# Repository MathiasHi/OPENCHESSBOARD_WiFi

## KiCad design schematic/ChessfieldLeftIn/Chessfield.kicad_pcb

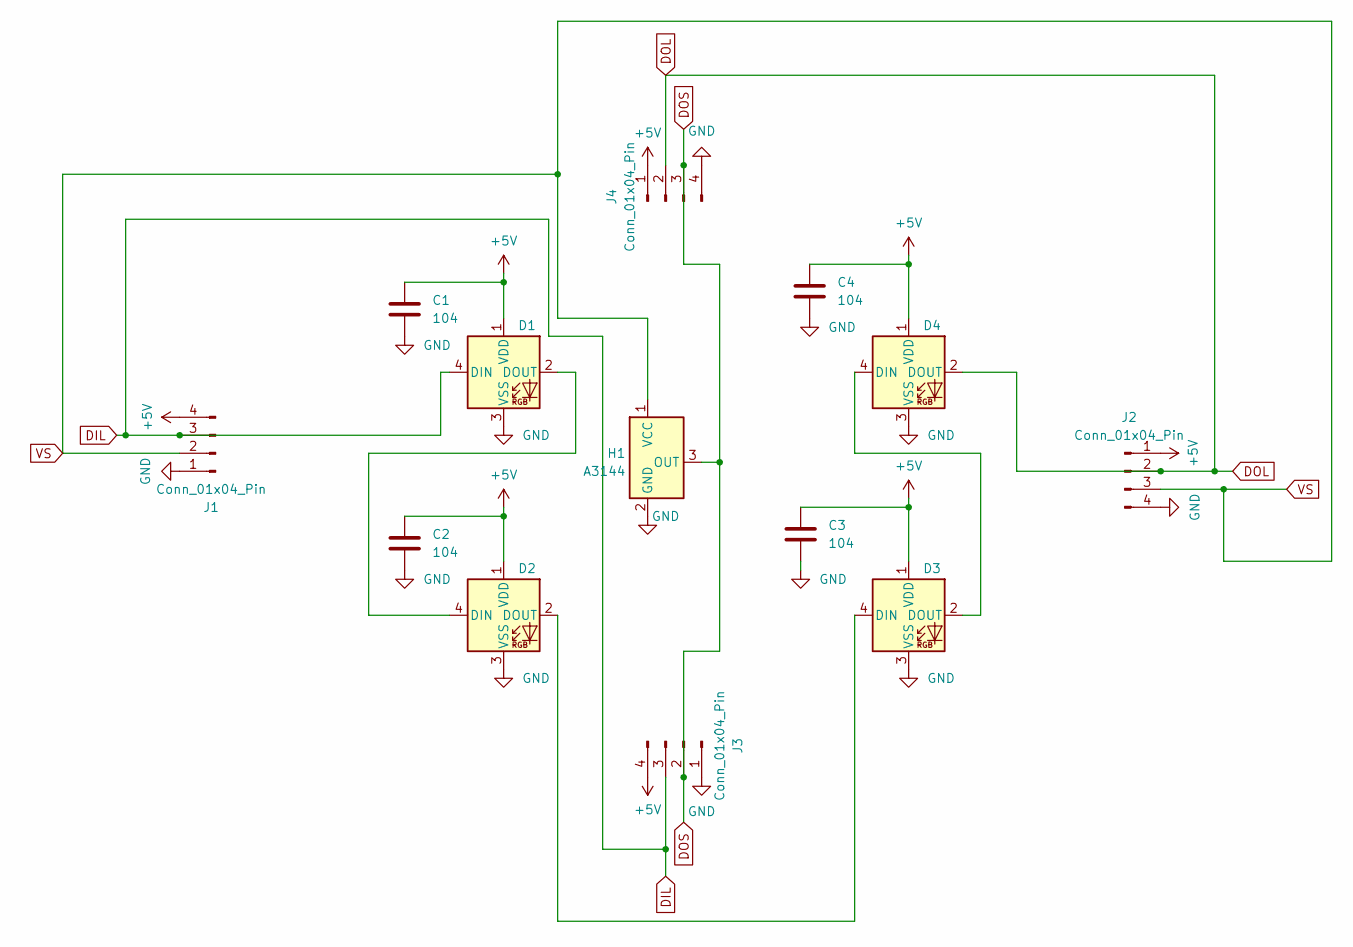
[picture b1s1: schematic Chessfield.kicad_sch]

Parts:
C1, C2, C3, C4: 104; C_0603_1608Metric_Pad1.08x0.95mm_HandSolder
D1, D2, D3, D4: WS2812B; LED_WS2812B_PLCC4_5.0x5.0mm_P3.2mm
H1: A3144; TO-92_Inline_Horizontal1
J1, J2, J3, J4: Conn_01x04_Pin; PinHeader_1x04_P2.54mm_Horizontal

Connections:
+5V: C1.1, C2.1, C3.1, C4.1, D1.1 (VDD), D2.1 (VDD), D3.1 (VDD), D4.1 (VDD), J1.4, J2.1, J3.4, J4.1
DIL: D1.4 (DIN), J1.3, J3.3
DOL: D4.2 (DOUT), J2.2, J4.2
DOS: H1.3 (OUT), J3.2, J4.3
GND: C1.2, C2.2, C3.2, C4.2, D1.3 (VSS), D2.3 (VSS), D3.3 (VSS), D4.3 (VSS), H1.2 (GND), J1.1, J2.4, J3.1, J4.4
unnamed: D1.2 (DOUT), D2.4 (DIN)
unnamed: D2.2 (DOUT), D3.4 (DIN)
unnamed: D3.2 (DOUT), D4.4 (DIN)
VS: H1.1 (VCC), J1.2, J2.3

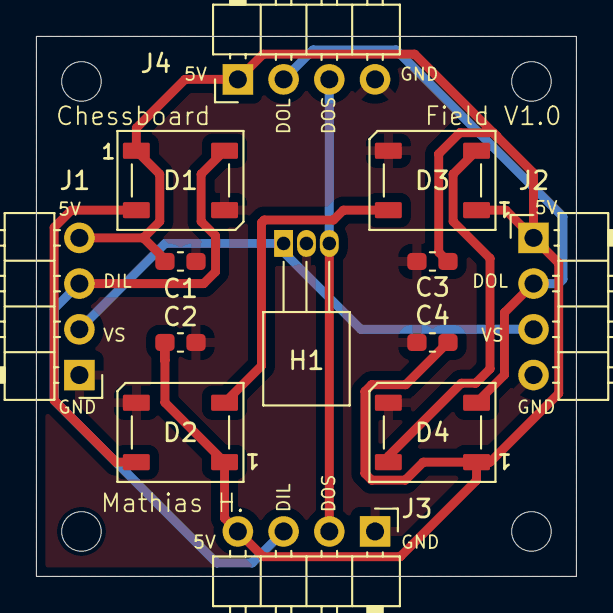
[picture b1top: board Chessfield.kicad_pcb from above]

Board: 2 copper layers, 30.0 x 30.0 mm, 13 parts (0 on the bottom side), 9 nets.

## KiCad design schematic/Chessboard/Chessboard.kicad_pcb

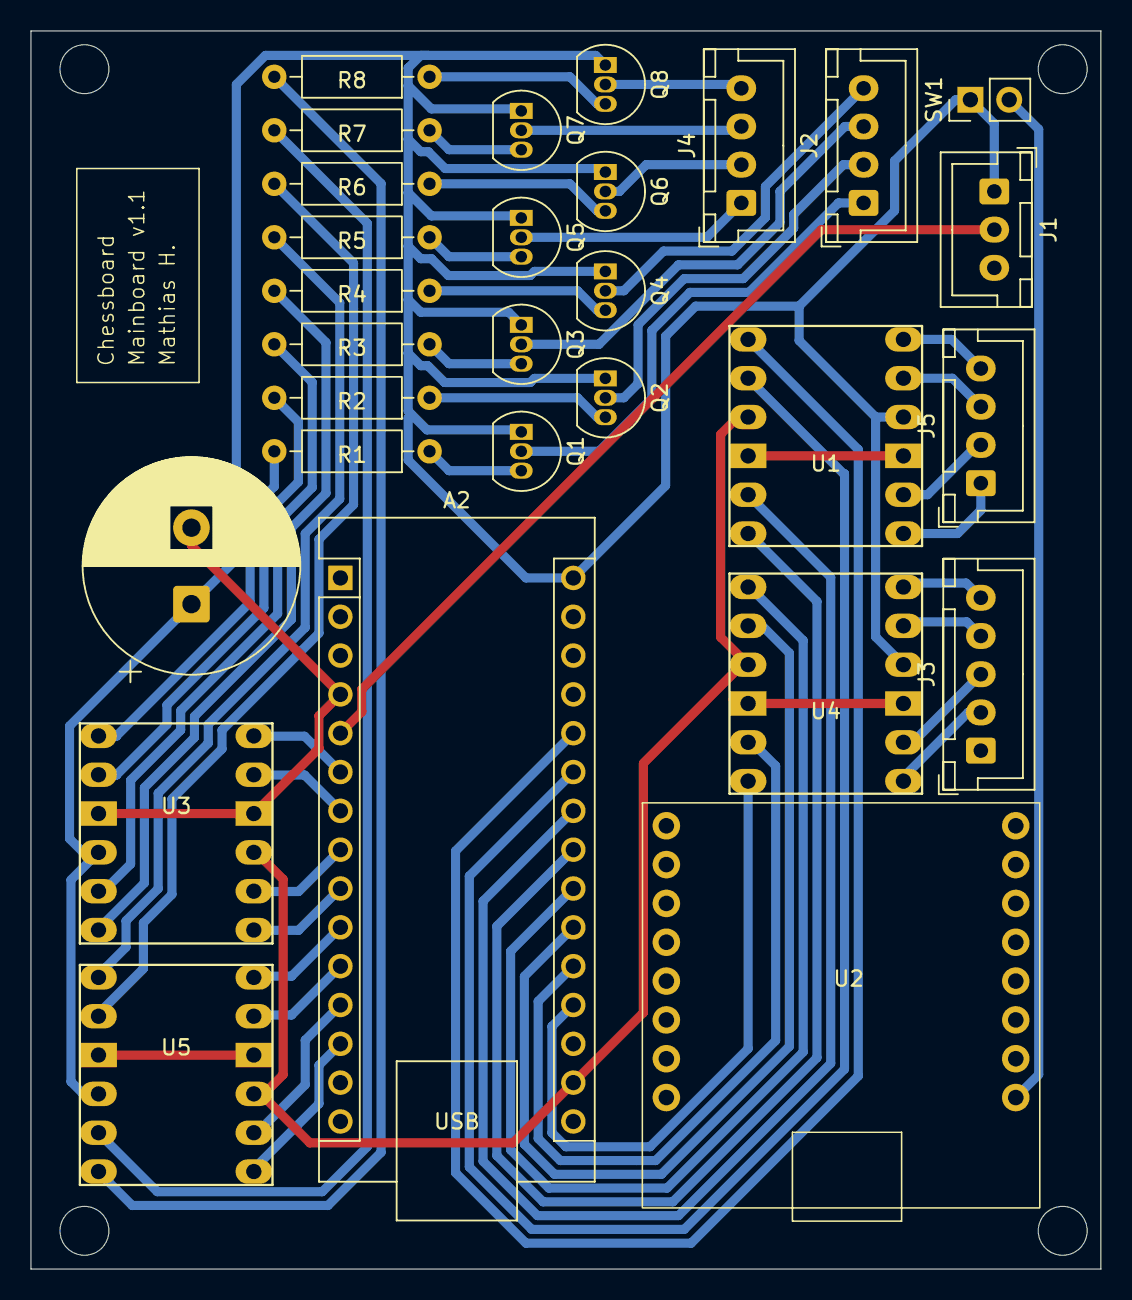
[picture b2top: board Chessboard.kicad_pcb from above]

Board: 2 copper layers, 70.0 x 81.0 mm, 29 parts (0 on the bottom side), 53 nets.

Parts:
A2: Arduino_Nano_ESP32; Arduino_Nano
C3: C_Polarized; CP_Radial_D14.0mm_P5.00mm
J1: LED; JST_XH_B3B-XH-A_1x03_P2.50mm_Vertical
J2, J4: VOUT; JST_XH_B4B-XH-A_1x04_P2.50mm_Vertical
J3: Data; JST_XH_B5B-XH-A_1x05_P2.50mm_Vertical
J5: Data; JST_XH_B4B-XH-A_1x04_P2.50mm_Vertical
Q1, Q2, Q3, Q4, Q5, Q6, Q7, Q8: BC640; TO-92_Inline
R1, R2, R3, R4, R5, R6, R7, R8: 2K2; R_Axial_DIN0207_L6.3mm_D2.5mm_P10.16mm_Horizontal
SW1: SW_SPST; PinHeader_1x02_P2.54mm_Vertical
U1, U3, U4, U5: Logic Level Shifter; LogicLevel4ch
U2: Batterie Shield; D1_mini_board

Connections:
+3V3: A2.17 (3V3), U1.10 (LV), U3.10 (LV), U4.10 (LV), U5.10 (LV)
+5V: A2.30 (VIN), C3.1, J1.1, Q1.1 (E), Q2.1 (E), Q3.1 (E), Q4.1 (E), Q5.1 (E), Q6.1 (E), Q7.1 (E), Q8.1 (E), SW1.1 (A), U1.3 (HV), U3.3 (HV), U4.3 (HV), U5.3 (HV)
/LED_ROW_1_2/LED_Data: A2.5 (D2), J1.2
/Sensor/D1: J5.1, U1.6 (HV4)
/Sensor/D2: J5.2, U1.5 (HV3)
/Sensor/D3: J5.3, U1.2 (HV2)
/Sensor/D4: J5.4, U1.1 (HV1)
/Sensor/D5: J3.2, U4.6 (HV4)
/Sensor/D6: J3.3, U4.5 (HV3)
/Sensor/D7: J3.4, U4.2 (HV2)
/Sensor/D8: J3.5, U4.1 (HV1)
/Sensor/VS1: J2.1, Q1.2 (C)
/Sensor/VS2: J2.2, Q2.2 (C)
/Sensor/VS3: J2.3, Q3.2 (C)
/Sensor/VS4: J2.4, Q4.2 (C)
/Sensor/VS5: J4.1, Q5.2 (C)
/Sensor/VS6: J4.2, Q6.2 (C)
/Sensor/VS7: J4.3, Q7.2 (C)
/Sensor/VS8: J4.4, Q8.2 (C)
GND: A2.4 (GND), A2.29 (GND), C3.2, J1.3, J3.1, U1.4 (GND), U1.9 (GND), U2.2 (GND), U3.4 (GND), U3.9 (GND), U4.4 (GND), U4.9 (GND), U5.4 (GND), U5.9 (GND)
unnamed: A2.19 (A0), U4.7 (LV4)
unnamed: A2.20 (A1), U4.8 (LV3)
unnamed: A2.21 (A2), U4.11 (LV2)
unnamed: A2.22 (A3), U4.12 (LV1)
unnamed: A2.25 (A6), U1.11 (LV2)
unnamed: A2.26 (A7), U1.12 (LV1)
unnamed: A2.6 (D3), U3.7 (LV4)
unnamed: A2.7 (D4), U3.8 (LV3)
unnamed: A2.8 (D5), U3.11 (LV2)
unnamed: A2.9 (D6), U3.12 (LV1)
unnamed: A2.10 (D7), U5.7 (LV4)
unnamed: A2.11 (D8), U5.8 (LV3)
unnamed: A2.12 (D9), U5.11 (LV2)
unnamed: A2.13 (D10/CS), U5.12 (LV1)
unnamed: A2.24 (SCL/A5), U1.8 (LV3)
unnamed: A2.23 (SDA/A4), U1.7 (LV4)
unnamed: Q1.3 (B), R1.1
unnamed: Q2.3 (B), R2.1
unnamed: Q3.3 (B), R3.1
unnamed: Q4.3 (B), R4.1
unnamed: Q5.3 (B), R5.1
unnamed: Q6.3 (B), R6.1
unnamed: Q7.3 (B), R7.1
unnamed: Q8.3 (B), R8.1
unnamed: SW1.2 (B), U2.1 (5V)
unnamed: R4.2, U3.1 (HV1)
unnamed: R3.2, U3.2 (HV2)
unnamed: R2.2, U3.5 (HV3)
unnamed: R1.2, U3.6 (HV4)
unnamed: R8.2, U5.1 (HV1)
unnamed: R7.2, U5.2 (HV2)
unnamed: R6.2, U5.5 (HV3)
unnamed: R5.2, U5.6 (HV4)

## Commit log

2025-03-31 Use led strip
2025-04-01 get hall inputs as intended
2025-04-26 use neo pixel lib, change led orientation
2025-04-26 set new limit
2025-04-29 light up all squares
2025-04-30 First time working wifi
2025-07-02 add schematic. use digital sensors
2025-07-03 fix Stream Buffer issue
2025-09-28 edit schematics
2025-10-04 routen and gerber files
2025-10-04 export schematics and images
2025-10-05 finish Mainboard design
2025-10-05 add chessfield schematics
2025-10-05 update chesssfield
2025-10-06 finish chessfield
2025-10-06 add documents and image
2025-10-06 fix chessfield schematics
2025-10-26 add left and right input field
2025-10-26 Fix move input, only wen piece put down
2025-12-06 Remove Plug on Top, fixes for new Hardware
2025-12-07 Fix startup issue
